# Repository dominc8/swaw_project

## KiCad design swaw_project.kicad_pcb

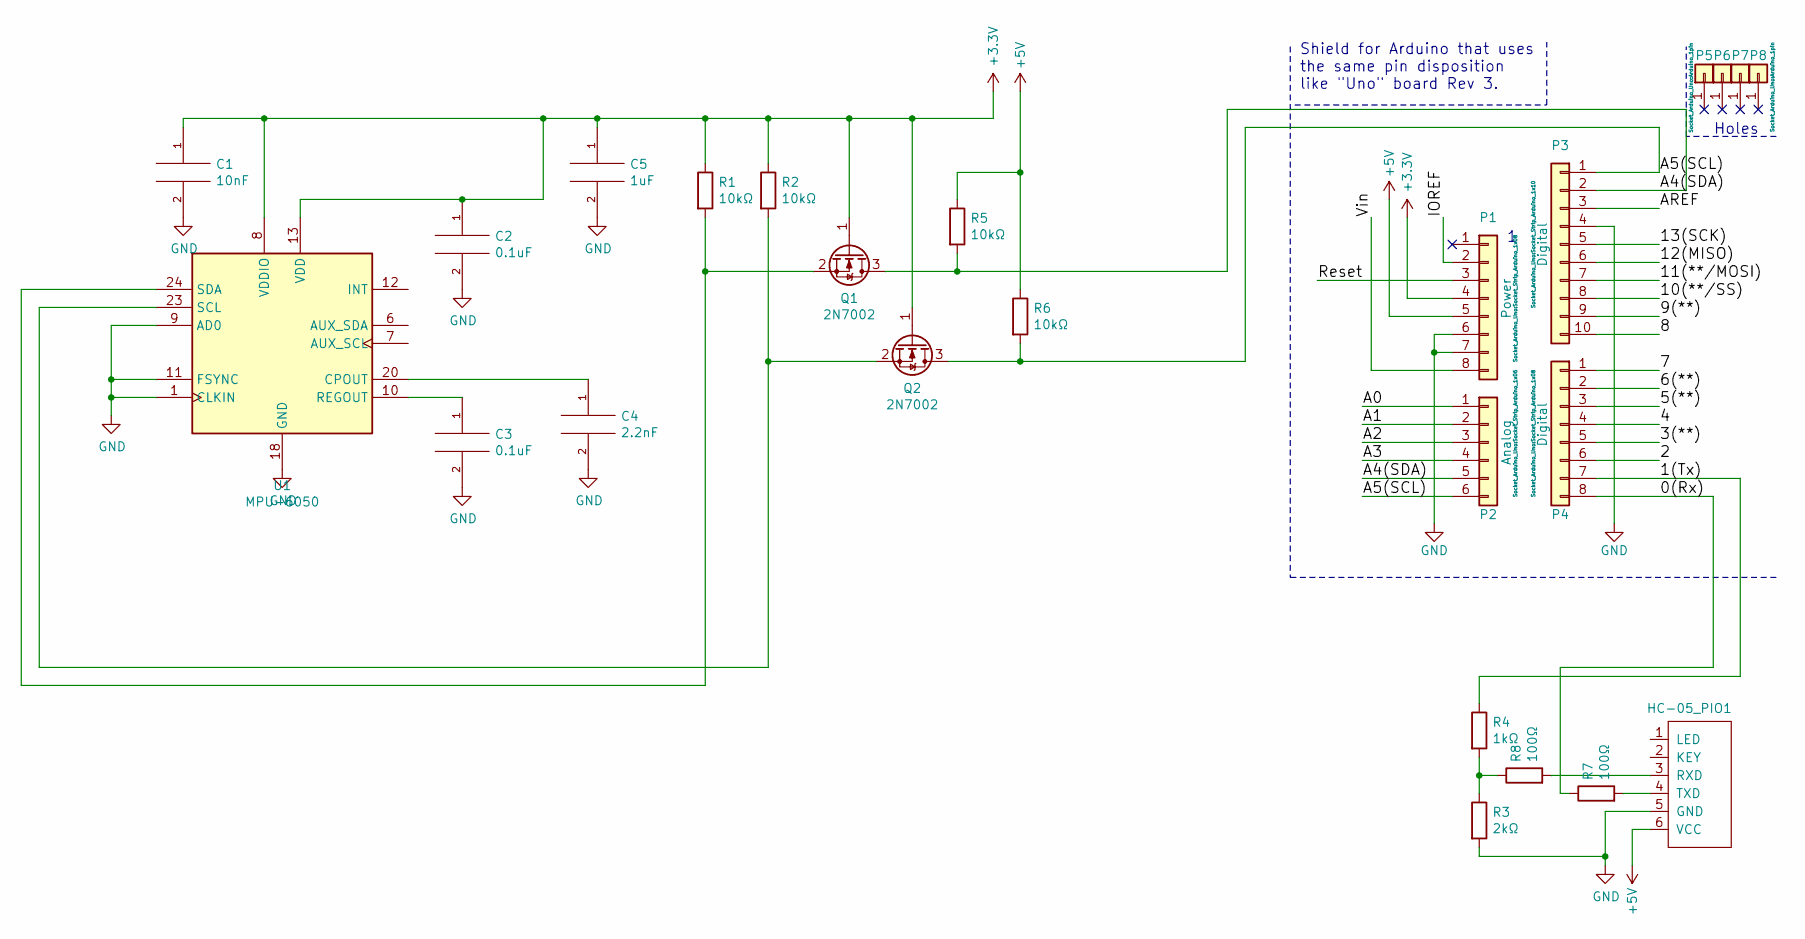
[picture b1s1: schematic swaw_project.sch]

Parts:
C1: 10nF; C_0805_2012Metric_Pad1.15x1.40mm_HandSolder
C2, C3: 0.1uF; C_1206_3216Metric_Pad1.42x1.75mm_HandSolder
C4: 2.2nF; C_0603_1608Metric_Pad1.05x0.95mm_HandSolder
C5: 1uF; C_1206_3216Metric_Pad1.42x1.75mm_HandSolder
HC-05_PIO1: Bluetooh_PIO; PinSocket_1x06_P2.54mm_Vertical
P1: Power; Socket_Strip_Arduino_1x08
P2: Analog; Socket_Strip_Arduino_1x06
P3: Digital; Socket_Strip_Arduino_1x10
P4: Digital; Socket_Strip_Arduino_1x08
P5, P6, P7, P8: CONN_01X01; Arduino_1pin
Q1, Q2: 2N7002; SOT-23
R1, R2, R5, R6: 10kΩ; R_0612_1632Metric_Pad1.18x3.40mm_HandSolder
R3: 2kΩ; R_0805_2012Metric_Pad1.15x1.40mm_HandSolder
R4: 1kΩ; R_0805_2012Metric_Pad1.15x1.40mm_HandSolder
R7, R8: 100Ω; R_0603_1608Metric_Pad1.05x0.95mm_HandSolder
U1: MPU-6050; InvenSense_QFN-24_4x4mm_P0.5mm

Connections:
+3V3: C1.1, C2.1, C5.1, P1.4, Q1.1 (G), Q2.1 (G), R1.1, R2.1, U1.8 (VDDIO), U1.13 (VDD)
+5V: HC-05_PIO1.6 (VCC), P1.5, R5.1, R6.1
/0(Rx): P4.8, R7.1
/1(Tx): P4.7, R4.1
/2: P4.6
/3(**): P4.5
/4: P4.4
/5(**): P4.3
/6(**): P4.2
/7: P4.1
/8: P3.10
/9(**): P3.9
/10(**/SS): P3.8
/11(**/MOSI): P3.7
/12(MISO): P3.6
/13(SCK): P3.5
/A0: P2.1
/A1: P2.2
/A2: P2.3
/A3: P2.4
/A4(SDA): P2.5, P3.2, Q1.3 (D), R5.2
/A5(SCL): P2.6, P3.1, Q2.3 (D), R6.2
/AREF: P3.3
/IOREF: P1.2
/Reset: P1.3
/Vin: P1.8
GND: C1.2, C2.2, C3.2, C4.2, C5.2, HC-05_PIO1.5 (GND), P1.6, P1.7, P3.4, R3.2, U1.1 (CLKIN), U1.9 (AD0), U1.11 (FSYNC), U1.18 (GND)
unnamed: C3.1, U1.10 (REGOUT)
unnamed: C4.1, U1.20 (CPOUT)
unnamed: HC-05_PIO1.3 (RXD), R8.2
unnamed: HC-05_PIO1.4 (TXD), R7.2
unnamed: Q1.2 (S), R1.2, U1.24 (SDA)
unnamed: Q2.2 (S), R2.2, U1.23 (SCL)
unnamed: R3.1, R4.2, R8.1

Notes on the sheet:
Holes
Shield for Arduino that uses the same pin disposition like "Uno" board Rev 3.

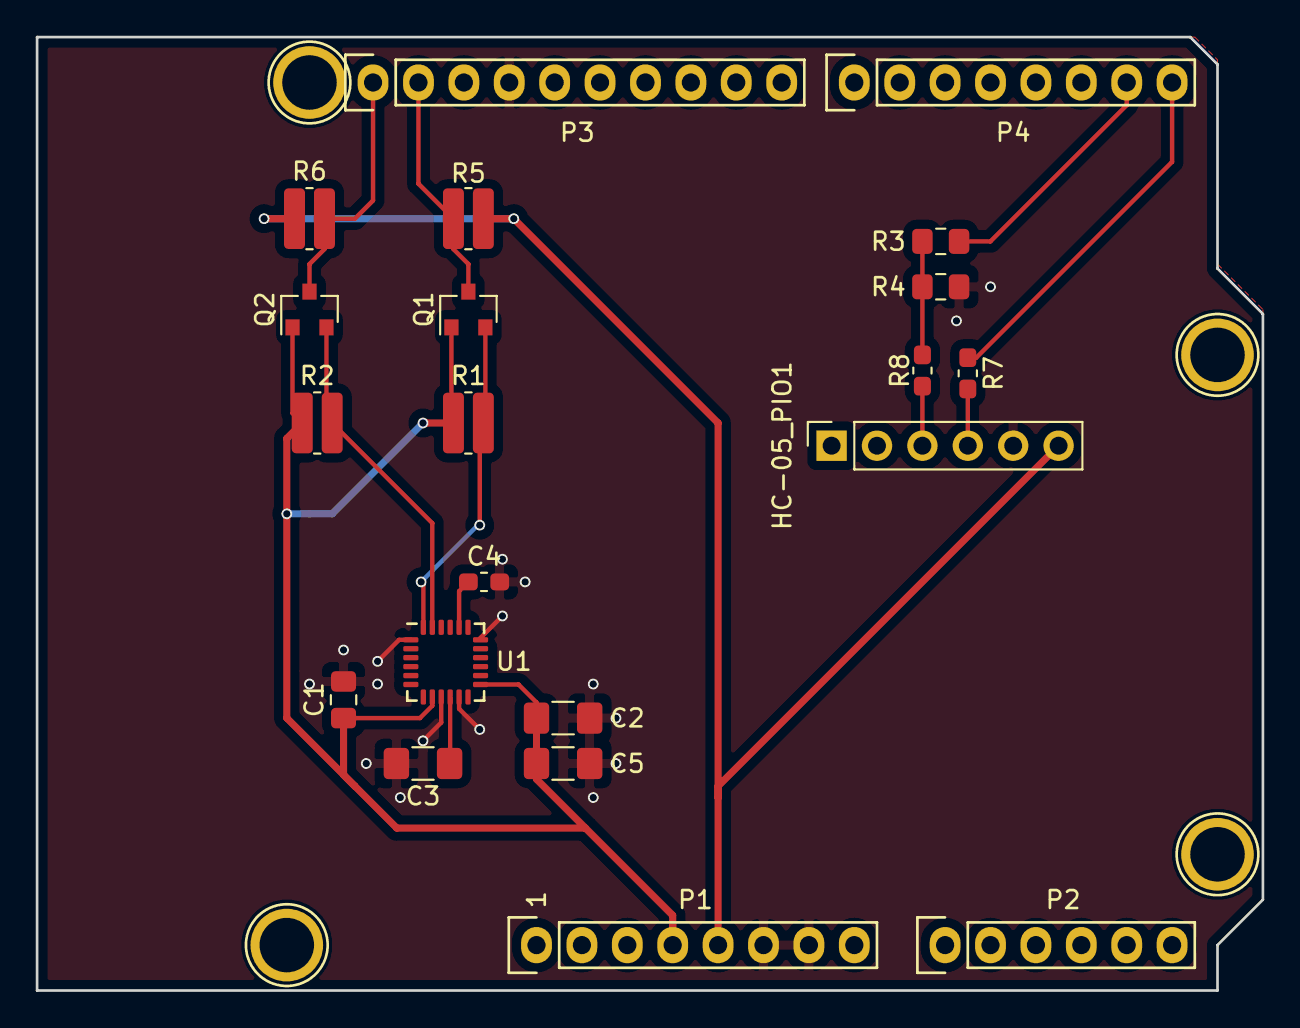
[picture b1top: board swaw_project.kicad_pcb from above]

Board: 2 copper layers, 68.6 x 53.3 mm, 25 parts (0 on the bottom side), 14 nets.

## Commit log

2020-04-28 init
2020-04-29 Add files via upload
    Bluetooth module scheme added to the library of project
2020-04-29 Added connection between MPU-6050 and Arduino
2020-04-29 Add files via upload
    Adding Bluetooth PIO, capacitors, resistors values and footprints
2020-04-30 Added logic shifters for i2c and basic pcb layout
2020-04-30 First version of layout
2020-04-30 Add files via upload
    Removing right angles for paths
2020-04-30 Adding changes to layout after review
2020-05-01 Fixed tx/rx connection, added gnd planes and some vias
2020-05-01 Moved pcb related things to separate folder
2020-05-30 Add handling of MPU - configuration and retrieving values
2020-06-03 Adding code for master and slave bluetooth in arduino ide
2020-06-08 Add all files generated by pycharm
2020-06-09 Changed some resistors to be normal size
2020-06-09 Added sampling with constant frequency 1kHz and computation of offset
2020-06-09 Added basic Bluetooth sending in mpu_handling
2020-06-09 Python script changed for int32 and modify arduino_test
2020-06-10 Python script changed for int32
2020-06-10 Hotfix - baudrate in python and arduino_test
2020-06-10 Tweaking bluetooh transfer
2020-06-24 Pythons few small changes
2020-06-24 Refactored code and moved final version to new folder
